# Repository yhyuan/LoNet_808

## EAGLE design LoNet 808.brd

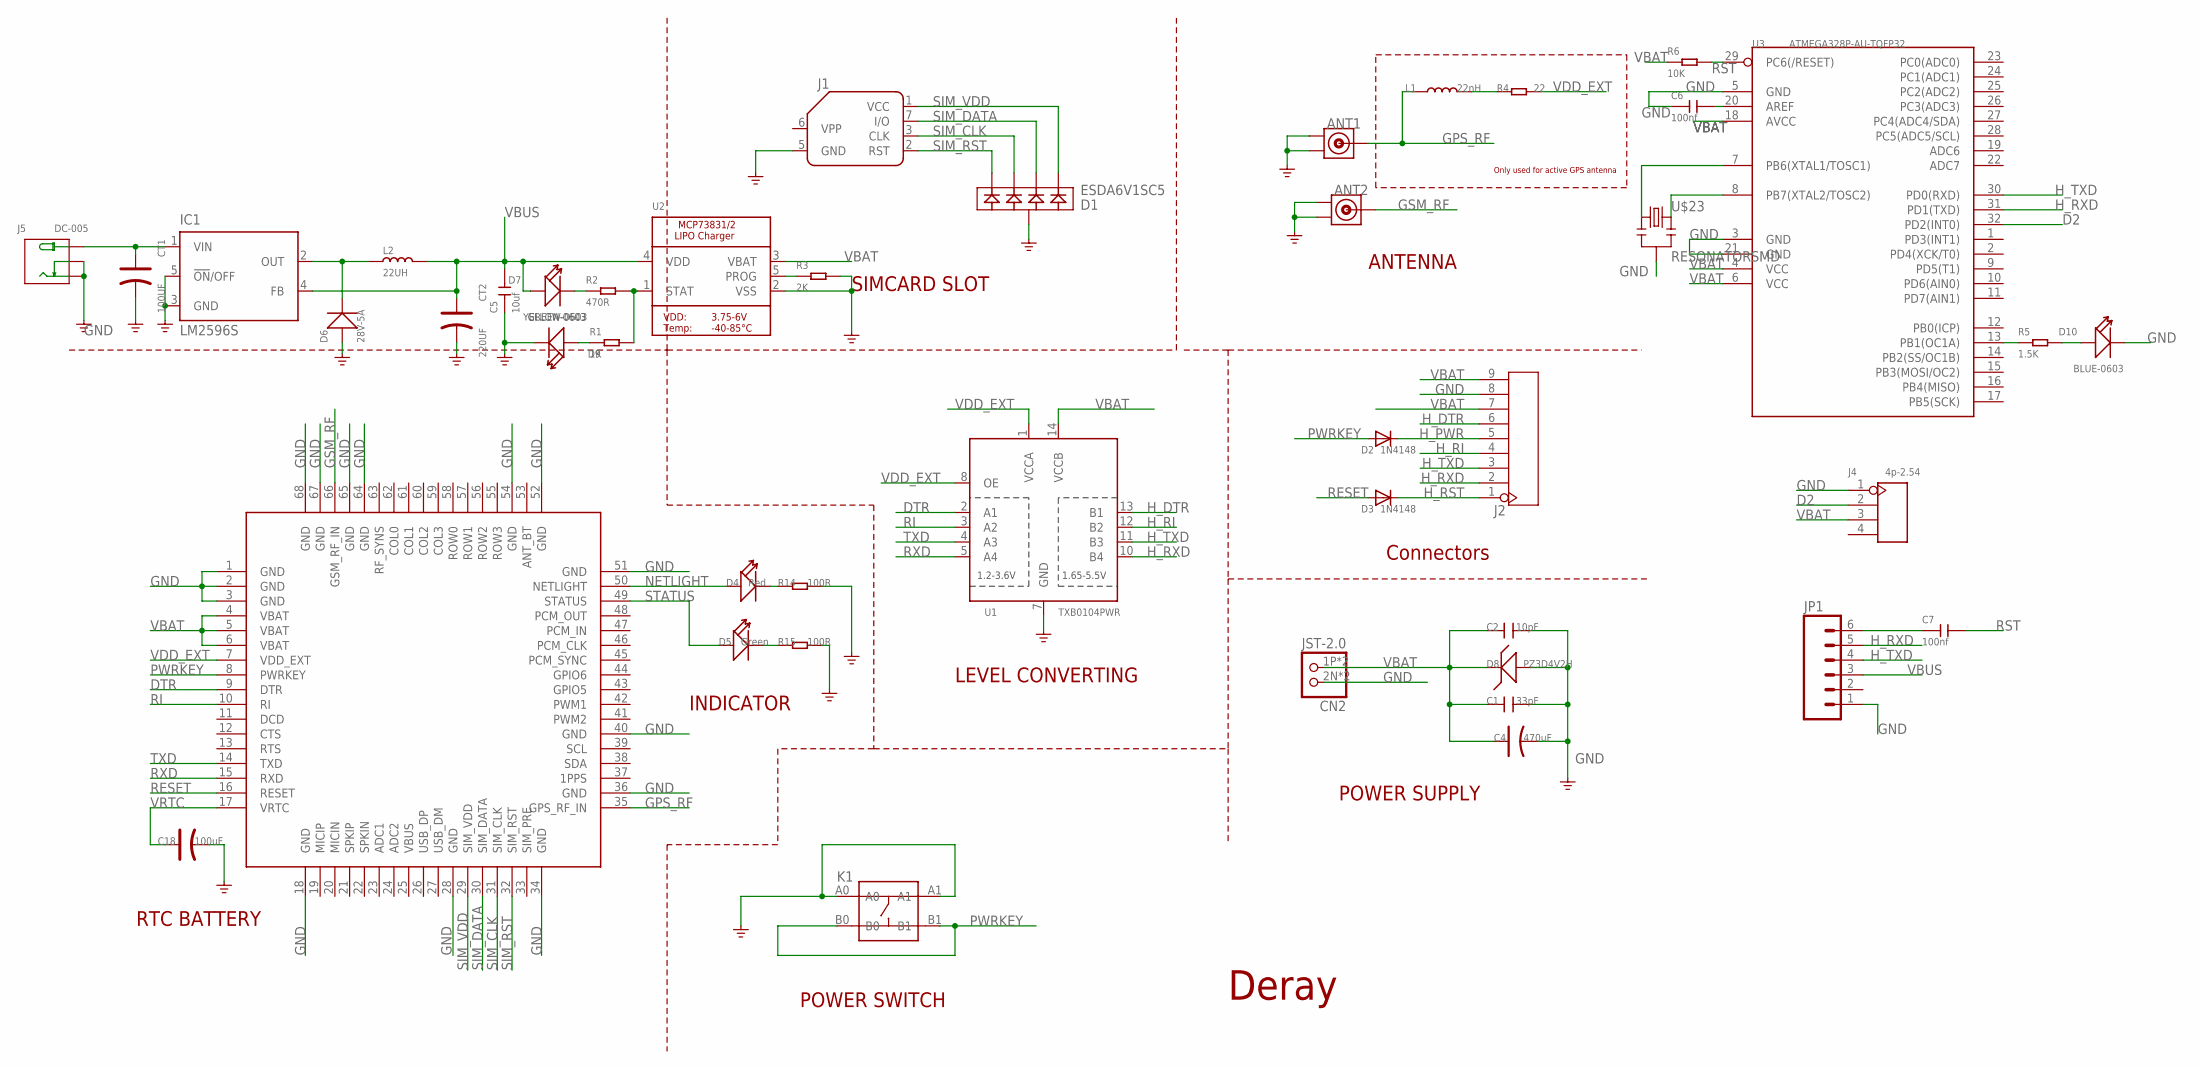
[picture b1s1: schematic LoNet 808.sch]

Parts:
ANT1, ANT2: ANTENNA-U-FL'3PAD-TYPE'; 3P-U-FL
C1: 33pF; 0603
C2: 10pF; 0603
C4: 470uF; AVX-D
C5: 10uf; C0603
C6, C7: 100nf; C0603
C18: 100uF; AVX-A
CN2: JST-2.0; JST-PH-2-SMT-RA2
CT1: 100UF; ELECTRO-SMD-C-6MM
CT2: 220UF; ELECTRO-SMD-C-6MM
D1: ESDA6V1SC5; SOT23-5L
D2, D3: 1N4148; SOD-323F
D4: Red; 0603
D5: Green; 0603
D6: 28V-5A; DO-214AA
D7: YELLOW-0603; LED-0603
D8: PZ3D4V2H; SOD-323F
D9: GREEN-0603; LED-0603
D10: BLUE-0603; LED-0603
IC1: LM2596S; TO263-5
J1: SIMHOLDERSIM; SIMHOLDER
J2: HEADER-9P-2.54; 9P-2.54
J4: 4p-2.54; H4-2.54
J5: DC-005; DCJ3P-14.2X11.0X9.0MM
JP1: M06SIP; 1X06
K1: BUTTON-4P-3.3X3.3; 4P-SMD-3.4X3.4X1.3H
L1: 22nH; L0402
L2: 22UH; SMD-2P-2.0X1.2X1.0MM
R1: 1K; R0603
R2: 470R; R0603
R3: 2K; R0603
R4: 22; R0402
R5: 1.5K; R0603
R6: 10K; R0603
R14, R15: 100R; 0603
U1: TXB0104PWR; TSSOP14
U2: MCP73831/2; SOT23-5
U3: ATMEGA328P-AU-TQFP32; TQFP32-0.8-7X7MM
U$1: SIM80868P-SMD-24X24; 68P-SMD-24X24
U$23: RESONATORSMD; RESONATOR-SMD

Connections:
D2: J4.2, U3.32 (PD2(INT0))
DTR: U1.2 (A1), U$1.9 (DTR)
GND: ANT1.GND1, ANT1.GND2, ANT2.GND1, ANT2.GND2, C1.2, C2.2, C4.-, C5.1, C6.1, C18.-, CN2.2N (1), CN2.4N (1), CT1.-, CT2.-, D1.2, D6.+, D8.A, D9.-, D10.-, IC1.3 (GND), IC1.5 (!ON!/OFF), J1.5 (GND), J2.8, J4.1, J5.-1 (-), J5.-2 (CDN), JP1.1, K1.A0, K1.A1, R3.2, R14.2, R15.2, U1.7 (GND), U2.2 (VSS), U3.3 (GND), U3.5 (GND), U3.21 (GND), U$1.1 (GND), U$1.2 (GND), U$1.3 (GND), U$1.18 (GND), U$1.28 (GND), U$1.34 (GND), U$1.36 (GND), U$1.40 (GND), U$1.51 (GND), U$1.52 (GND), U$1.54 (GND), U$1.64 (GND), U$1.65 (GND), U$1.67 (GND), U$1.68 (GND), U$23.2
GPS_RF: ANT1.D, L1.1, U$1.35 (GPS_RF_IN)
GSM_RF: ANT2.D, U$1.66 (GSM_RF_IN)
H_DTR: J2.6, U1.13 (B1)
H_PWR: D2.C, J2.5
H_RI: J2.4, U1.12 (B2)
H_RST: D3.C, J2.1
H_RXD: J2.2, JP1.5, U1.10 (B4), U3.31 (PD1(TXD))
H_TXD: J2.3, JP1.4, U1.11 (B3), U3.30 (PD0(RXD))
unnamed: CT1.+, IC1.1 (VIN), J5.+
unnamed: D6.-, IC1.2 (OUT), L2.1
unnamed: R1.2, R2.2, U2.1 (STAT)
unnamed: R3.1, U2.5 (PROG)
unnamed: L1.2, R4.1
unnamed: D7.-, R2.1
unnamed: D4.-, R14.1
unnamed: D5.-, R15.1
unnamed: C6.2, U3.20 (AREF)
unnamed: D9.+, R1.1
unnamed: R5.1, U3.13 (PB1(OC1A))
unnamed: D10.+, R5.2
unnamed: U3.7 (PB6(XTAL1/TOSC1)), U$23.1
unnamed: U3.8 (PB7(XTAL2/TOSC2)), U$23.3
unnamed: C7.1, JP1.6
NETLIGHT: D4.+, U$1.50 (NETLIGHT)
PWRKEY: D2.A, K1.B0, K1.B1, U$1.8 (PWRKEY)
RESET: D3.A, U$1.16 (RESET)
RI: U1.3 (A2), U$1.10 (RI)
RST: C7.2, R6.2, U3.29 (PC6(/RESET))
RXD: U1.5 (A4), U$1.15 (RXD)
SIM_CLK: D1.3, J1.3 (CLK), U$1.31 (SIM_CLK)
SIM_DATA: D1.5, J1.7 (I/O), U$1.30 (SIM_DATA)
SIM_RST: D1.1, J1.2 (RST), U$1.32 (SIM_RST)
SIM_VDD: D1.4, J1.1 (VCC), U$1.29 (SIM_VDD)
STATUS: D5.+, U$1.49 (STATUS)
TXD: U1.4 (A3), U$1.14 (TXD)
VBAT: C1.1, C2.1, C4.+, CN2.1P (2), CN2.3P (2), D8.C, J2.7, J2.9, J4.3, R6.1, U1.14 (VCCB), U2.3 (VBAT), U3.4 (VCC), U3.6 (VCC), U3.18 (AVCC), U$1.4 (VBAT), U$1.5 (VBAT), U$1.6 (VBAT)
VBUS: C5.2, CT2.+, D7.+, IC1.4 (FB), JP1.3, L2.2, U2.4 (VDD)
VDD_EXT: R4.2, U1.1 (VCCA), U1.8 (OE), U$1.7 (VDD_EXT)
VRTC: C18.+, U$1.17 (VRTC)

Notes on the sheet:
POWER SUPPLY
SIMCARD SLOT
POWER SWITCH
ANTENNA
INDICATOR
RTC BATTERY
LEVEL CONVERTING
Connectors
Deray
Only used for active GPS antenna

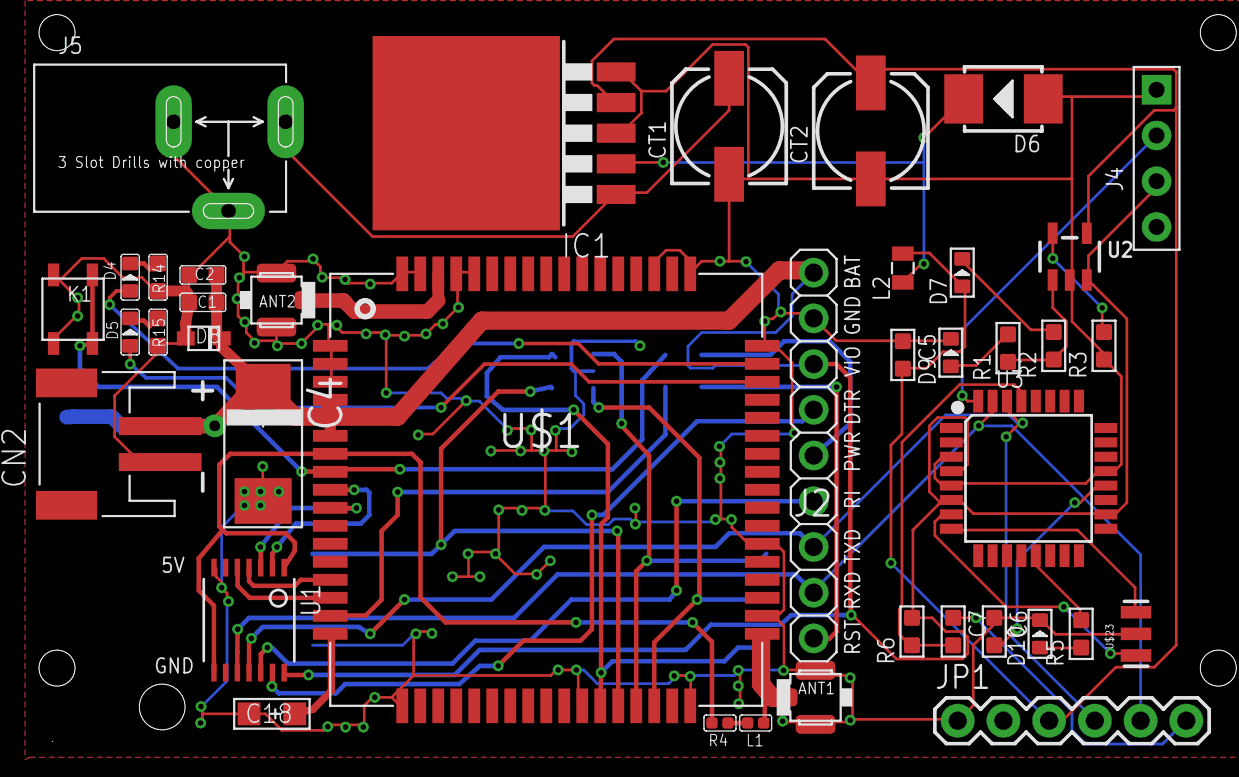
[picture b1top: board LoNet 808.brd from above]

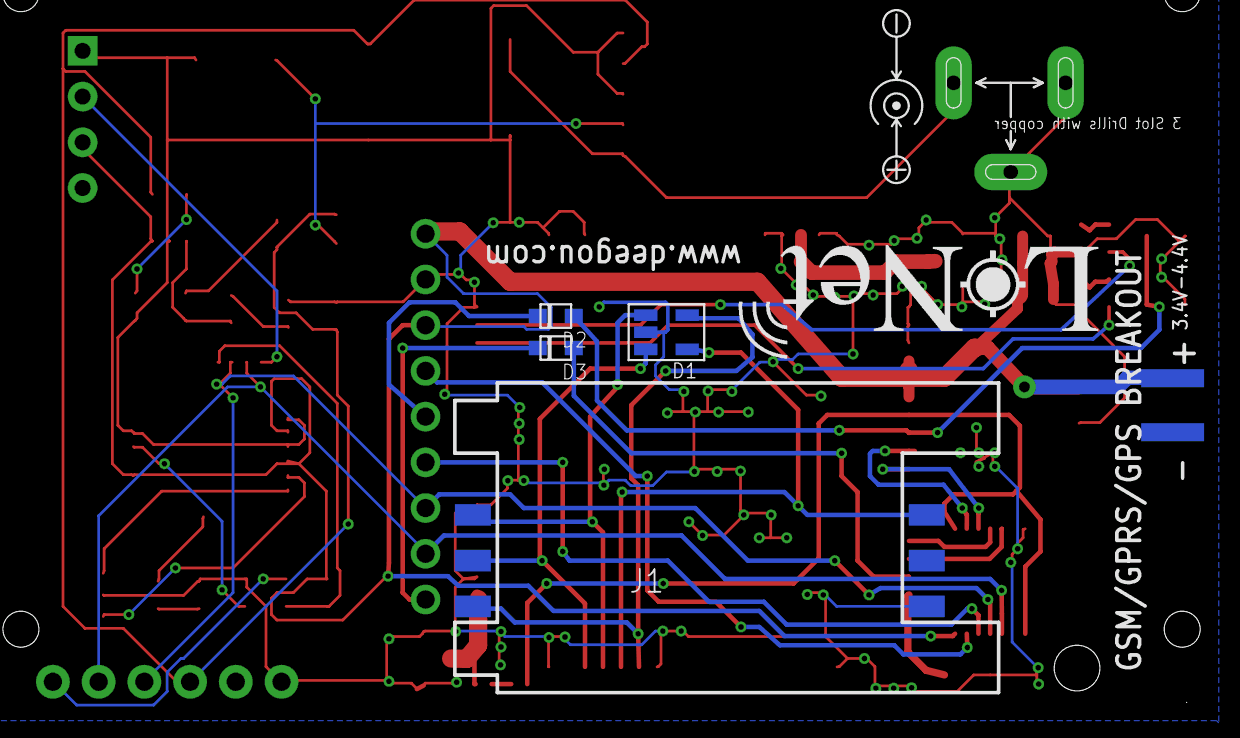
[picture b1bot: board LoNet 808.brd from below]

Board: 2 copper layers, 44 parts (4 on the bottom side), 42 nets.

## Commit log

2016-01-14 init
2016-01-14 add components
2016-01-14 lm2596
2016-01-14 datasheet.pdf
2016-01-14 add more
2016-01-15 add mcu
2016-01-15 more connection
2016-01-19 add RFM83C
2016-01-20 get berber files
2016-01-22 Gerber files
2016-01-22 brd file

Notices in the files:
parts and their libraries:
SparkFun-Connectors: Licensing: Creative Commons ShareAlike 4.0 International - https://creativecommons.org/licenses/by-sa/4.0
Aesthetics: Released under the Creative Commons
Aesthetics: https://creativecommons.org/licenses/by-sa/4.0
